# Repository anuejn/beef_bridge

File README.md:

# BEEF BRIDGE

An IGBT-half-bridge-board that can handle High Voltages (450V) and high current (15A Hot, 30A Cold).

The board also features a LC-lowpass-filter, that has a cutoff frequency of about 20khz. The purpose of this board is to serve as the Power-Stage of a beefy class-d audio amplifier.

The design is open hardware and licensed under CERN-OHL-S.

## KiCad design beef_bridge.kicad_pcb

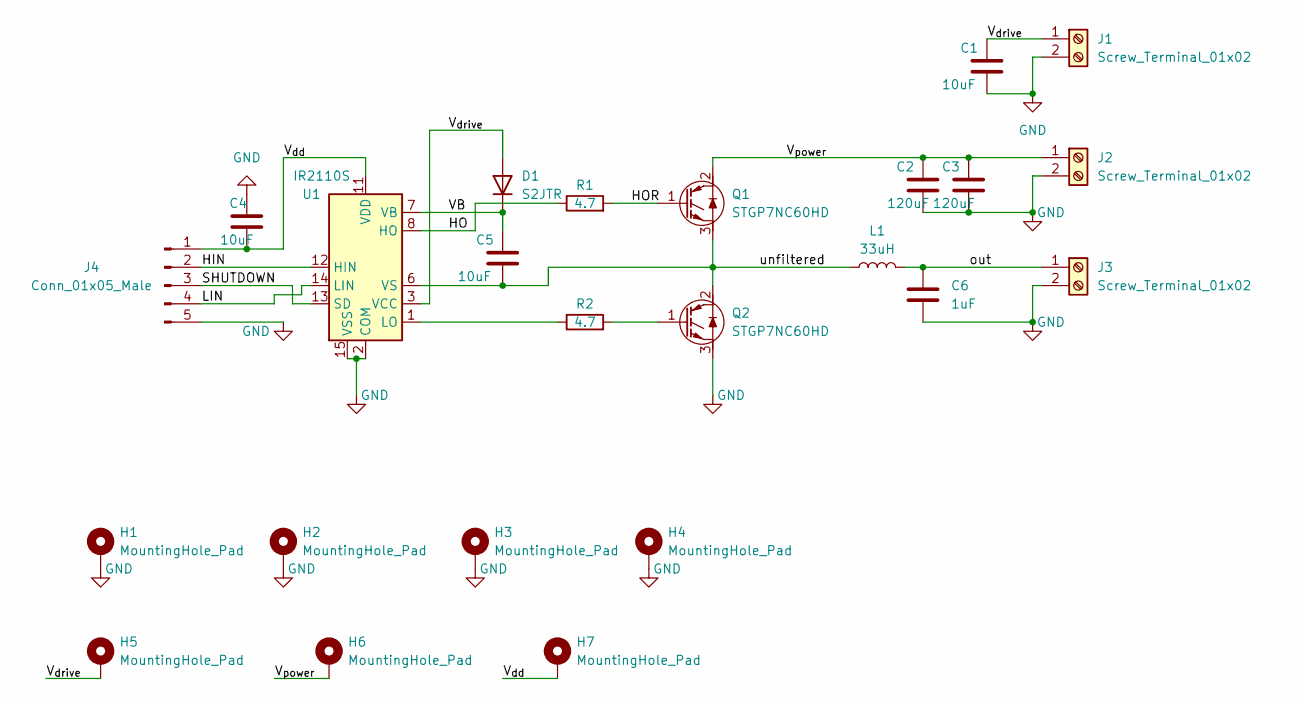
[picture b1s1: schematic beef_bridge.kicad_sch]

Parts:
C1, C4, C5: 10uF; C_1206_3216Metric
C2, C3: 120uF; CP_Radial_D18.0mm_P7.50mm
C6: 1uF; C_Rect_L31.5mm_W9.0mm_P27.50mm_MKS4
D1: S2JTR; D_SMB
H1, H2, H3, H4, H5, H6, H7: MountingHole_Pad; MountingHole_3.2mm_M3_Pad_Via
J1, J2, J3: Screw_Terminal_01x02; TerminalBlock_Phoenix_MKDS-1,5-2_1x02_P5.00mm_Horizontal
J4: Conn_01x05_Male; PinHeader_1x05_P2.54mm_Vertical
L1: 33uH; L_Toroid_Vertical_L31.8mm_W15.9mm_P13.50mm_Bourns_5700
Q1, Q2: STGP7NC60HD; TO-220-3_Vertical
R1, R2: 4.7; R_0603_1608Metric
U1: IR2110S; SOIC-16W_7.5x10.3mm_P1.27mm

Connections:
/HIN: J4.2, U1.12 (HIN)
/HO: R1.1, U1.8 (HO)
/HOR: Q1.1 (G), R1.2
/LIN: J4.4, U1.14 (LIN)
/SHUTDOWN: J4.3, U1.13 (SD)
/VB: C5.1, D1.1 (K), U1.7 (VB)
/V_{dd}: C4.2, H7.1, J4.1, U1.11 (VDD)
/V_{drive}: C1.1, D1.2 (A), H5.1, J1.1, U1.3 (VCC)
/V_{power}: C2.1, C3.1, H6.1, J2.1, Q1.2 (C)
/out: C6.1, J3.1, L1.2
/unfiltered: C5.2, L1.1, Q1.3 (E), Q2.2 (C), U1.6 (VS)
GND: C1.2, C2.2, C3.2, C4.1, C6.2, H1.1, H2.1, H3.1, H4.1, J1.2, J2.2, J3.2, J4.5, Q2.3 (E), U1.2 (COM), U1.15 (VSS)
unnamed: Q2.1 (G), R2.2
unnamed: R2.1, U1.1 (LO)

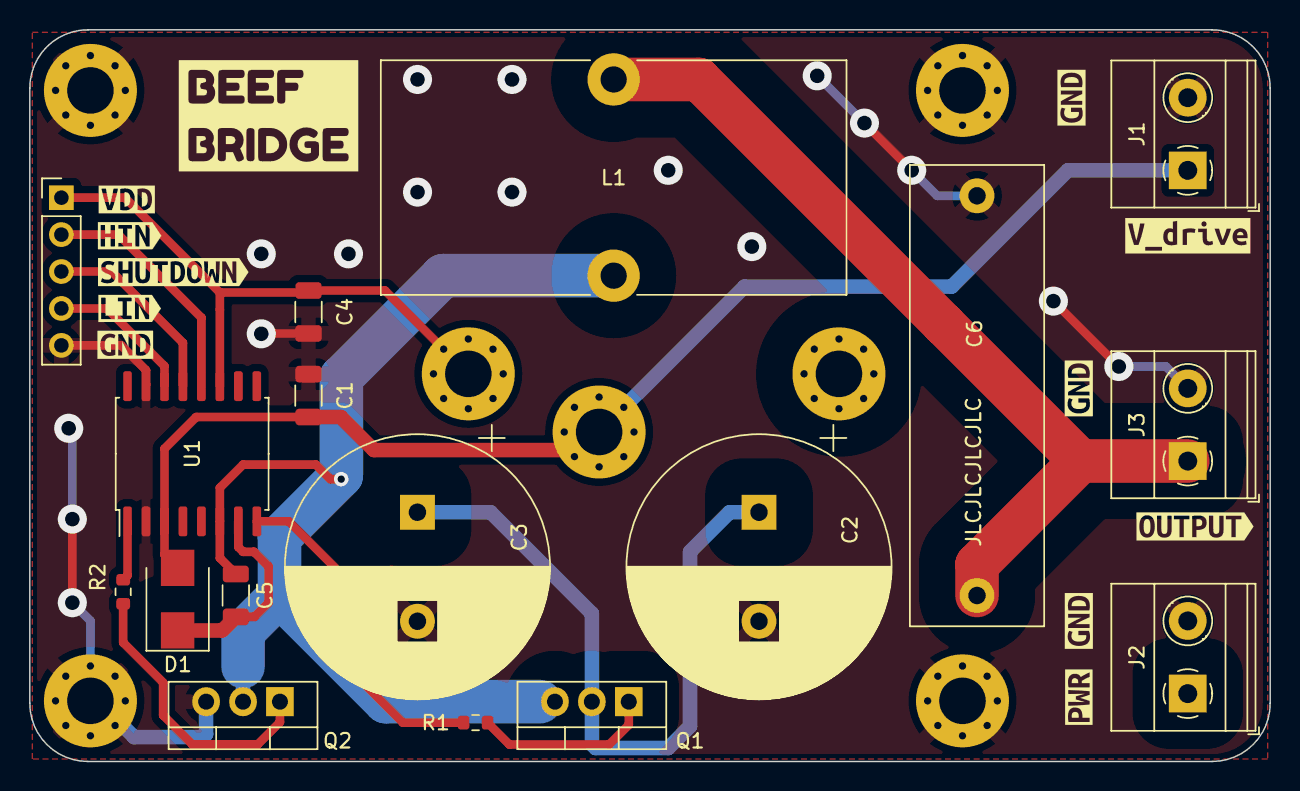
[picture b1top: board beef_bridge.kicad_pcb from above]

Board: 2 copper layers, 85.3 x 50.3 mm, 36 parts (0 on the bottom side), 14 nets.

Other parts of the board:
kibuzzard-62C4B9B2: G***; kibuzzard-62C4B9B2
kibuzzard-62C4B9BD: G***; kibuzzard-62C4B9BD
kibuzzard-62C4B9F5, kibuzzard-62C4B9F5#2, kibuzzard-62C4B9F5#3, kibuzzard-62C4B9F5#4: G***; kibuzzard-62C4B9F5
kibuzzard-62C4B9F9: G***; kibuzzard-62C4B9F9
kibuzzard-62C57BCB: G***; kibuzzard-62C57BCB
kibuzzard-62C57CCB: G***; kibuzzard-62C57CCB
kibuzzard-62C59C38: G***; kibuzzard-62C59C38
kibuzzard-62C59CAE: G***; kibuzzard-62C59CAE
kibuzzard-62C59E44: G***; kibuzzard-62C59E44

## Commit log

2022-07-07 add rendering
